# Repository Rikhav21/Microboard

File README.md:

# Microboard
# About
So this is a devboard that I made because I lose wires to upload code to my arduinos all the time, so I just wanted to make a devboard where you can just plug it into the computer, and run suff. So one that that you will probably notice it that I swapped out the USB recepticle for a USB plug, and I also just tried to utilize as much of the IO as possible. Also I think that I never actually saw a squre devboard, so I also tried to make it a unique shape. In the rengers you can not see the USB-C plug, so I will update with pictures when I actually build it. 

# Schematic
So hile making the schematic, I think that it looks pretty similar to most other devboards. As I said before, I tried to use all of the pins on the MUCH, so everything is used.

# PCB
This was actually my first time using vias, and having to reroute something so many times. It was also my first time uring pours, but that made it a lot easier. I tried to get most of the routing done on the front, but there are some vias to the back of the PCB.

# Making
So for building this I am ordering the PCB from JLCPCB and all of the other components from LCSC. I am going to hald solder all of the components, but you could do PCBA. The cost should be around $26, but that is counting all of the MOQs, realistically you coulb proabably make 5 of them while spending less than $39 and the majority of the cost is in shipping.

# BOM
| Mfr. | Order Qty. | Unit Price(USD) | Ext. Price(USD) | Package | Description | Product Link |
|------|------------|----------------|----------------|---------|-------------|--------------|
| Samsung Electro-Mechanics | 20 | 0.0101 | 0.20 | 0805 | 10uF 0805 Ceramic Capacitors | [Link](https://www.lcsc.com/product-detail/C15850.html) |
| FH | 100 | 0.0031 | 0.31 | 0603 | 15pF 0603 Ceramic Capacitors | [Link](https://www.lcsc.com/product-detail/C91703.html) |
| Raspberry Pi | 1 | 0.9440 | 0.94 | LQFN-56(7x7) |  | [Link](https://www.lcsc.com/product-detail/C2040.html) |
| Hong Cheng | 5 | 0.0805 | 0.40 | Through Hole, Right Angle, P=2.54mm | Right Angle, P=2.54mm Headers, Male Pins RoHS | [Link](https://www.lcsc.com/product-detail/C41376120.html) |
| YAGEO | 100 | 0.0006 | 0.06 | 0402 | 10kΩ 0402 Resistor | [Link](https://www.lcsc.com/product-detail/C60490.html) |
| YAGEO | 100 | 0.0006 | 0.06 | 0402 | 1kΩ 0402 Resistor | [Link](https://www.lcsc.com/product-detail/C106235.html) |
| Huiyuan crystal | 10 | 0.0603 | 0.60 | SMD3225-4P | Crystal Oscillator 20pF SMD3225-4P | [Link](https://www.lcsc.com/product-detail/C5265859.html) |
| Winbond | 1 | 1.6062 | 1.61 | SOIC-8-208mil | 128Mbit 2.7V~3.6V 133MHz SPI SOIC-8 | [Link](https://www.lcsc.com/product-detail/C97521.html) |
| UNI-ROYAL | 100 | 0.0006 | 0.06 | 0402 | 27Ω 0402 Resistor | [Link](https://www.lcsc.com/product-detail/C25100.html) |
| UNI-ROYAL | 100 | 0.0005 | 0.05 | 0402 | 5.1kΩ 0402 Resistor | [Link](https://www.lcsc.com/product-detail/C25905.html) |
| YAGEO | 100 | 0.0009 | 0.09 | 0402 | 100nF 0402 Ceramic Capacitors | [Link](https://www.lcsc.com/product-detail/C60474.html) |
| ALPSALPINE | 5 | 0.1277 | 0.64 | SMD, 3.9x2.9mm | Round Button 3.9mm SPST | [Link](https://www.lcsc.com/product-detail/C115357.html) |
| Samsung Electro-Mechanics | 100 | 0.0030 | 0.30 | 0402 | 25V 1uF X5R ±10% 0402 Ceramic Capacitors RoHS | [Link](https://www.lcsc.com/product-detail/C52923.html) |
| MICROCHIP | 1 | 0.5422 | 0.54 | SOT-89-3 | Fixed 3.3V SOT-89-3 Voltage Regulator | [Link](https://www.lcsc.com/product-detail/C632000.html) |
| MOLEX | 1 | 1.1995 | 1.20 | SMD | 1 24P -30℃~+85℃ Type-C SMD USB | [Link](https://www.lcsc.com/product-detail/C561769.html) |
|PCB+Shipping  |  |  |$5.12  |  |  |  |
|LCSC shipping + handling total  |   ||$18.59  |  |  |  |
|Total  |  |  |$25.28   |  |  |  |

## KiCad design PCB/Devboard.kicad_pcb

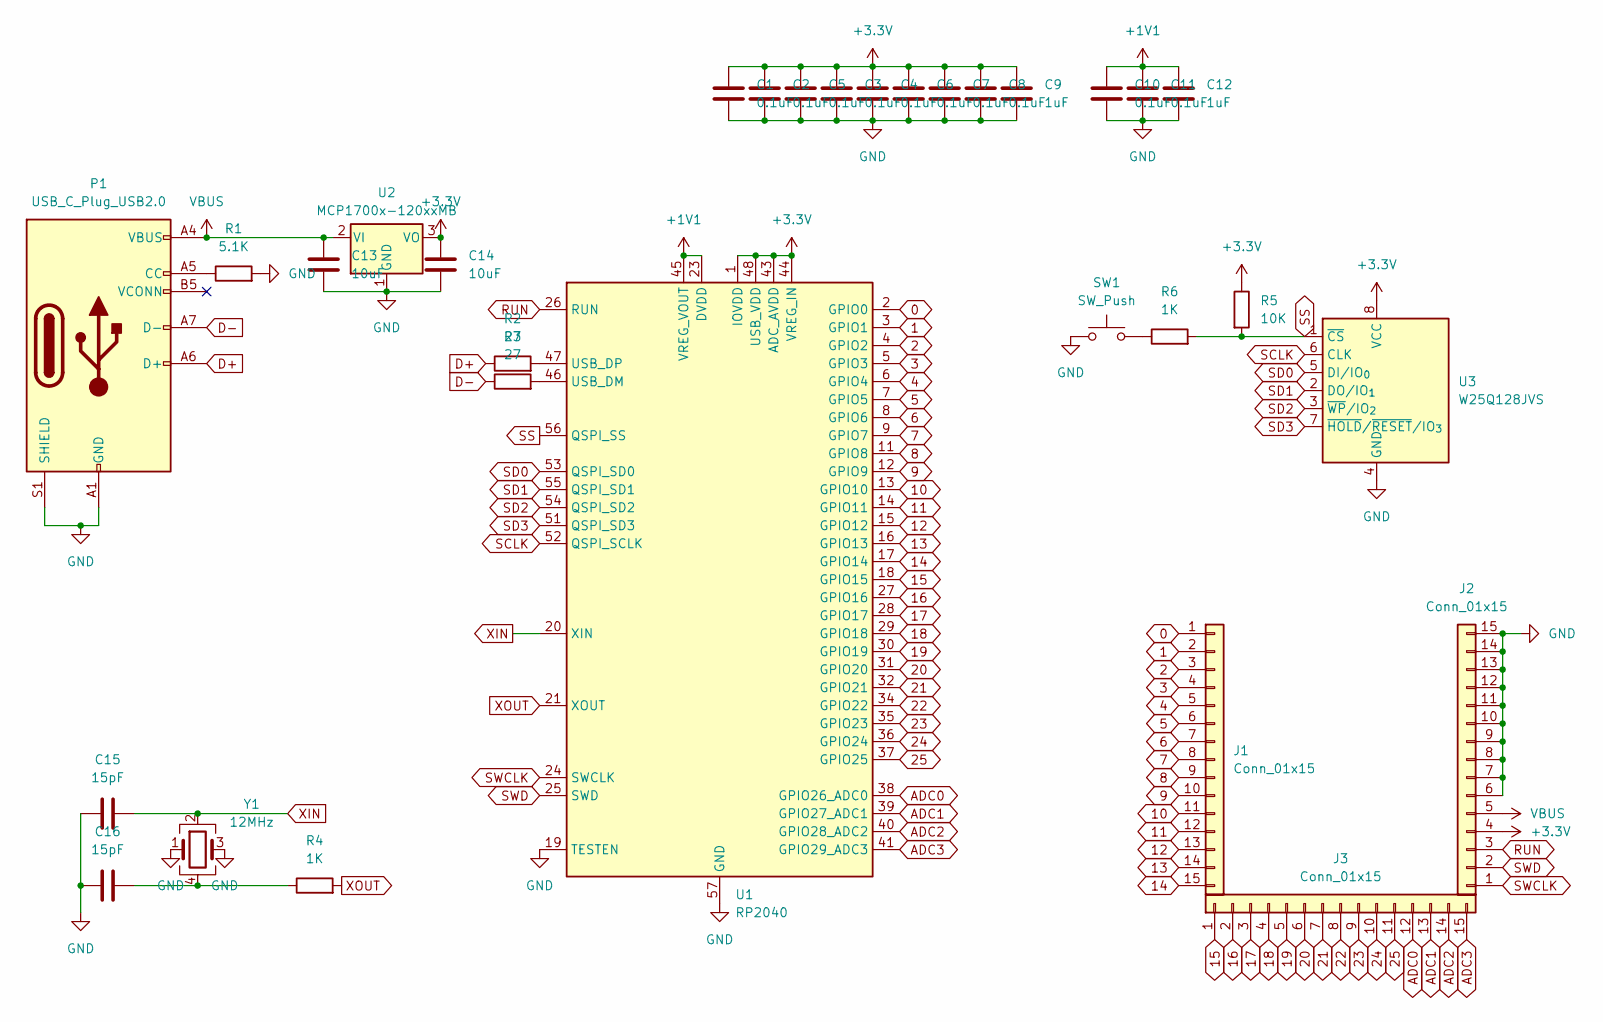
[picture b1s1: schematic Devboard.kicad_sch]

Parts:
C1, C2, C3, C4, C5, C6, C7, C8, C10, C11: 0.1uF; C_0402_1005Metric_Pad0.74x0.62mm_HandSolder
C9, C12: 1uF; C_0402_1005Metric_Pad0.74x0.62mm_HandSolder
C13, C14: 10uF; C_0201_0603Metric_Pad0.64x0.40mm_HandSolder
C15, C16: 15pF; C_0201_0603Metric_Pad0.64x0.40mm_HandSolder
J1, J2, J3: Conn_01x15; PinHeader_1x15_P2.54mm_Vertical
P1: USB_C_Plug_USB2.0; USB_C_Plug_ShenzhenJingTuoJin_918-118A2021Y40002_Vertical
R1: 5.1K; R_0402_1005Metric
R2, R3: 27; R_0402_1005Metric
R4, R6: 1K; R_0402_1005Metric
R5: 10K; R_0402_1005Metric
SW1: SW_Push; SW_Push_SPST_NO_Alps_SKRK
U1: RP2040; QFN-56-1EP_7x7mm_P0.4mm_EP3.2x3.2mm
U2: MCP1700x-120xxMB; SOT-89-3
U3: W25Q128JVS; SOIC-8_5.3x5.3mm_P1.27mm
Y1: 12MHz; Crystal_SMD_3225-4Pin_3.2x2.5mm_HandSoldering

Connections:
0: J1.1, U1.2 (GPIO0)
1: J1.2, U1.3 (GPIO1)
2: J1.3, U1.4 (GPIO2)
3: J1.4, U1.5 (GPIO3)
4: J1.5, U1.6 (GPIO4)
5: J1.6, U1.7 (GPIO5)
6: J1.7, U1.8 (GPIO6)
7: J1.8, U1.9 (GPIO7)
8: J1.9, U1.11 (GPIO8)
9: J1.10, U1.12 (GPIO9)
10: J1.11, U1.13 (GPIO10)
11: J1.12, U1.14 (GPIO11)
12: J1.13, U1.15 (GPIO12)
13: J1.14, U1.16 (GPIO13)
14: J1.15, U1.17 (GPIO14)
15: J3.1, U1.18 (GPIO15)
16: J3.2, U1.27 (GPIO16)
17: J3.3, U1.28 (GPIO17)
18: J3.4, U1.29 (GPIO18)
19: J3.5, U1.30 (GPIO19)
20: J3.6, U1.31 (GPIO20)
21: J3.7, U1.32 (GPIO21)
22: J3.8, U1.34 (GPIO22)
23: J3.9, U1.35 (GPIO23)
24: J3.10, U1.36 (GPIO24)
25: J3.11, U1.37 (GPIO25)
+1V1: C10.1, C11.1, C12.1, U1.23 (DVDD), U1.45 (VREG_VOUT), U1.50 (DVDD)
+3.3V: C1.1, C2.1, C3.1, C4.1, C5.1, C6.1, C7.1, C8.1, C9.1, C14.1, J2.4, R5.1, U1.1 (IOVDD), U1.10 (IOVDD), U1.22 (IOVDD), U1.33 (IOVDD), U1.42 (IOVDD), U1.43 (ADC_AVDD), U1.44 (VREG_IN), U1.48 (USB_VDD), U1.49 (IOVDD), U2.3 (VO), U3.8 (VCC)
ADC0: J3.12, U1.38 (GPIO26_ADC0)
ADC1: J3.13, U1.39 (GPIO27_ADC1)
ADC2: J3.14, U1.40 (GPIO28_ADC2)
ADC3: J3.15, U1.41 (GPIO29_ADC3)
D+: P1.A6 (D+), R2.1
D-: P1.A7 (D-), R3.1
GND: C1.2, C2.2, C3.2, C4.2, C5.2, C6.2, C7.2, C8.2, C9.2, C10.2, C11.2, C12.2, C13.2, C14.2, C15.1, C16.1, J2.6, J2.7, J2.8, J2.9, J2.10, J2.11, J2.12, J2.13, J2.14, J2.15, P1.A1 (GND), P1.A12 (GND), P1.B1 (GND), P1.B12 (GND), P1.S1 (SHIELD), R1.2, SW1.1, U1.19 (TESTEN), U1.57 (GND), U2.1 (GND), U3.4 (GND), Y1.1, Y1.3
unnamed: C16.2, R4.1, Y1.4
unnamed: P1.A5 (CC), R1.1
unnamed: R6.1, SW1.2
unnamed: R3.2, U1.46 (USB_DM)
unnamed: R2.2, U1.47 (USB_DP)
RUN: J2.3, U1.26 (RUN)
SCLK: U1.52 (QSPI_SCLK), U3.6 (CLK)
SD0: U1.53 (QSPI_SD0), U3.5 (DI/IO_{0})
SD1: U1.55 (QSPI_SD1), U3.2 (DO/IO_{1})
SD2: U1.54 (QSPI_SD2), U3.3 (~WP/IO_{2})
SD3: U1.51 (QSPI_SD3), U3.7 (~HOLD/~RESET/IO_{3})
SS: R5.2, R6.2, U1.56 (QSPI_SS), U3.1 (~CS)
SWCLK: J2.1, U1.24 (SWCLK)
SWD: J2.2, U1.25 (SWD)
VBUS: C13.1, J2.5, P1.A4 (VBUS), P1.A9 (VBUS), P1.B4 (VBUS), P1.B9 (VBUS), U2.2 (VI)
XIN: C15.2, U1.20 (XIN), Y1.2
XOUT: R4.2, U1.21 (XOUT)

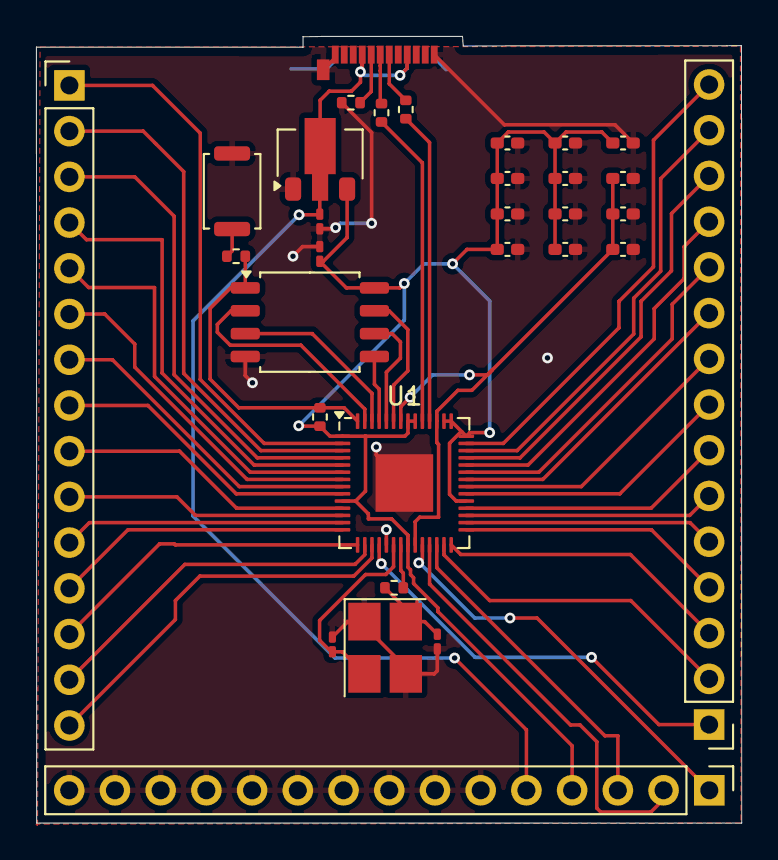
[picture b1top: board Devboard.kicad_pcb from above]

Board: 2 copper layers, 39.2 x 43.7 mm, 31 parts (0 on the bottom side), 52 nets.

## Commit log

2025-11-25 Expand README with project details and BOM
    Added detailed sections about the project, including the about, schematic, PCB, making process, and BOM with links to components.
